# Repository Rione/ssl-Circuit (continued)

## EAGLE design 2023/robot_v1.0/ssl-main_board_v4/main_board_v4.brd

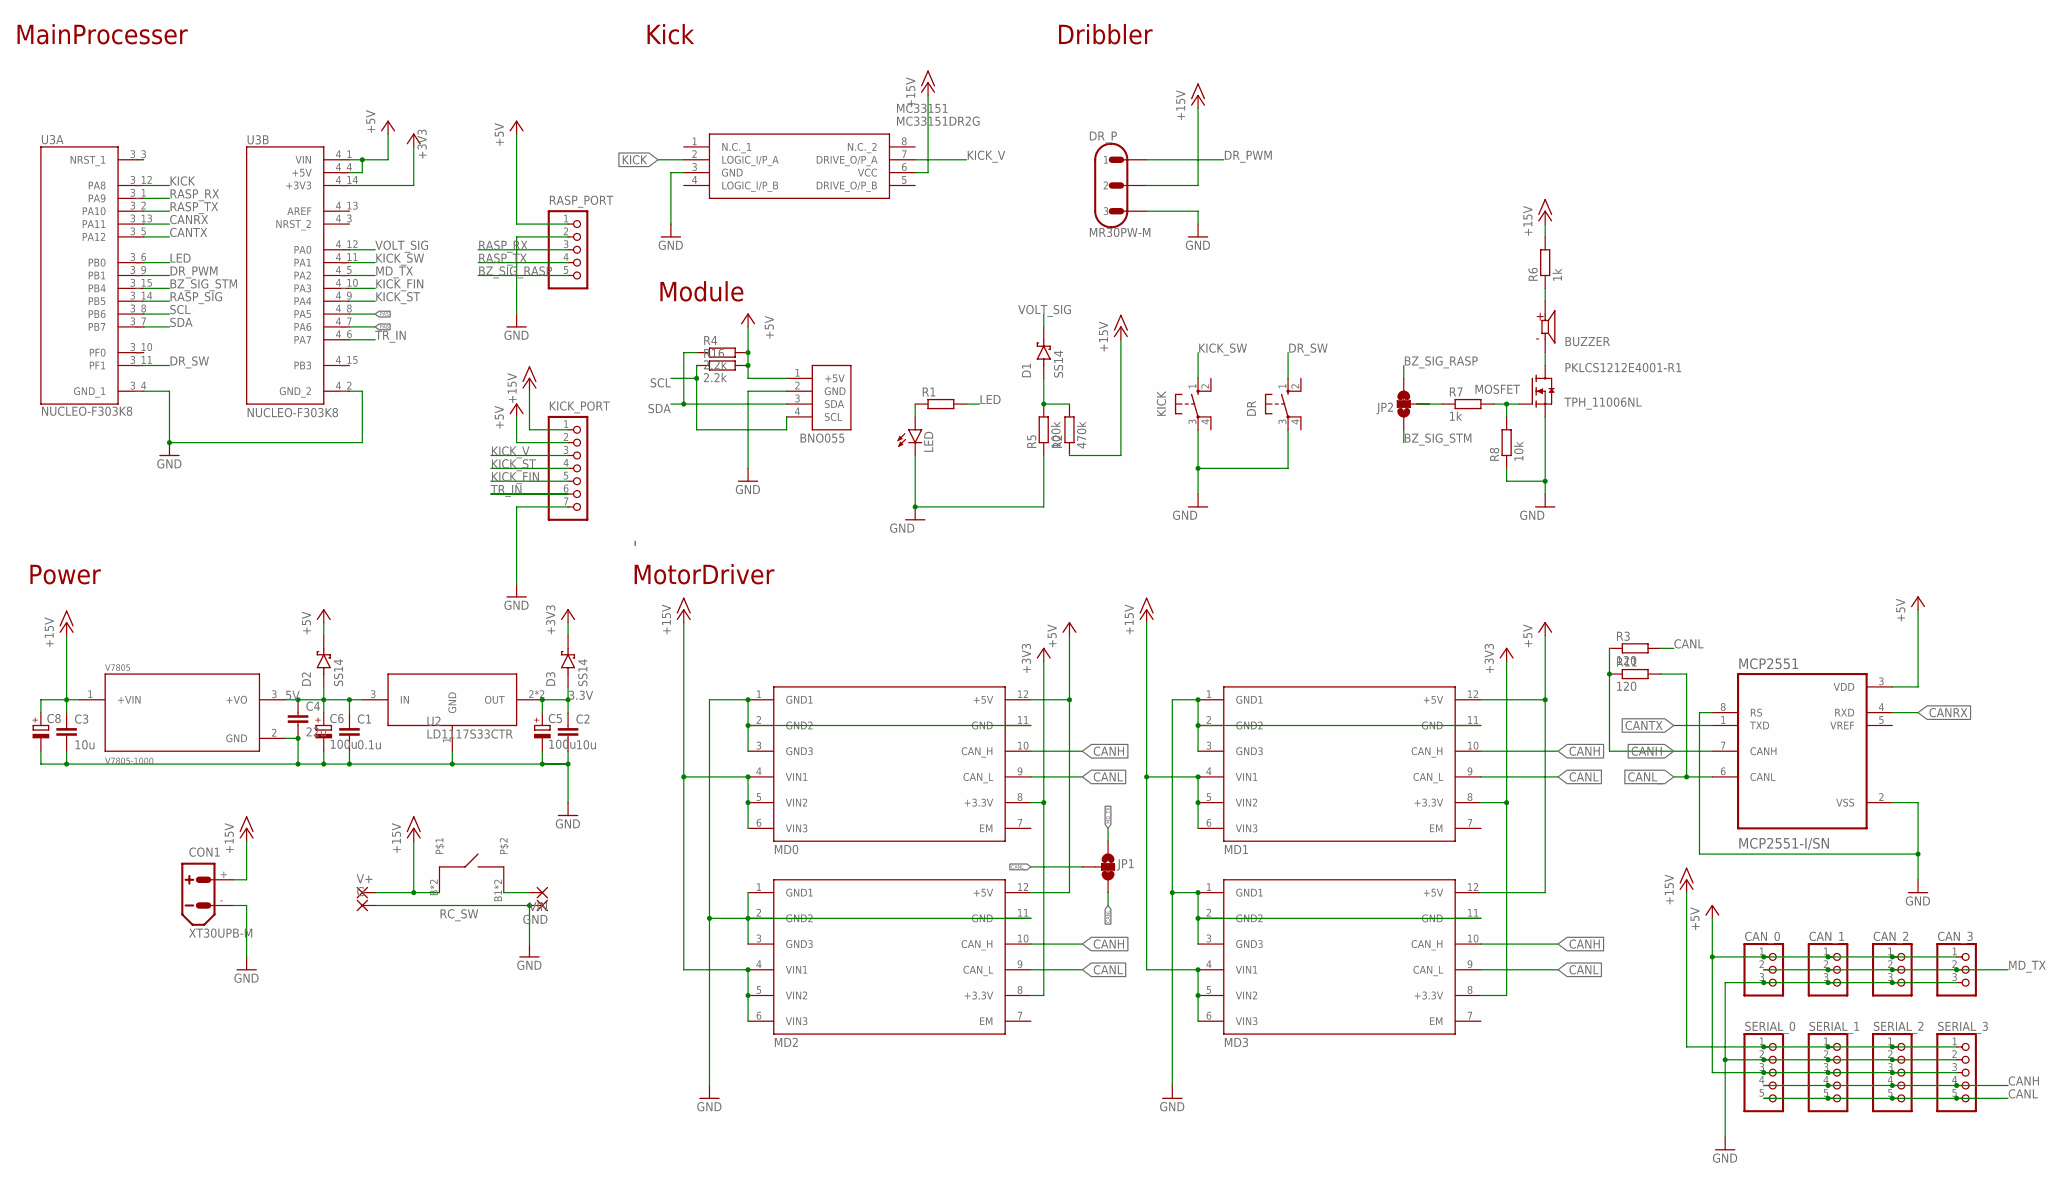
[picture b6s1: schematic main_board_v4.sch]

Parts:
BUZZER: PKLCS1212E4001-R1; SPKR_PKLCS1212E4001-R1
C1: 0.1u; C1608
C2, C3: 10u; C1608
C4: 22u; C2012
C5, C6: 100u; 153CLV-0605
C8: CPOL-EU140CLH-1010; 140CLH-1010
CAN_0, CAN_1, CAN_2, CAN_3: PINHD-1X3; 1X03
CON1: XT30UPB-M
D1, D2, D3: SS14; DIOM4325X250N
DR: 10-XX; B3F-10XX
DR_P: MR30PW-M
G: SMD2; SMD1,27-2,54
GND: SMD5; SMD2,54-5,08
JP1, JP2: JUMPER-SMT_3_1-NC_TRACE_SILK; SMT-JUMPER_3_1-NC_TRACE_SILK
KICK: 10-XX; B3F-10XX
KICK_PORT: S7B-XH-A
LED: LEDCHIP-LED0805; CHIP-LED0805
MC33151: MC33151DR2G; SOIC127P600X175-8N
MCP2551: MCP2551-I/SN; SOIC127P599X175-8N
MD0, MD1, MD2, MD3: MD_ROOTS
MOSFET: TPH_11006NL; TRANS_TPHR8504PL,L1Q
R1: R-EU_R0603; R0603
R2: 470k; R0603
R3, R11: 120; R0603
R4, R16: 2.2k; R0603
R5: 100k; R0603
R6, R7: 1k; R0603
R8: 10k; R0603
RASP_PORT: B5B-XH-A
SERIAL_0, SERIAL_1, SERIAL_2, SERIAL_3: PINHD-1X5; 1X05
U2: LD1117S33CTR; SOT223
U3: NUCLEO-F303K8; MODULE_NUCLEO-F303K8
U$1: BNO055
U$2: ROCKER_SW; MILLING
V7805: V7805-1000; CONV_V7805-1000
V+: SMD2; SMD1,27-2,54
VIN: SMD5; SMD2,54-5,08

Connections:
2: D1.A, R2.2, R5.2
3.3V: C2.1, C5.+, D3.A, U2.2 (OUT), U2.4 (OUT)
5V: C1.1, C4.1, C6.+, D2.A, U2.3 (IN), V7805.3 (+VO)
+3V3: D3.C (K), MD0.8 (+3.3V), MD1.8 (+3.3V), MD2.8 (+3.3V), MD3.8 (+3.3V), U3.4_14 (+3V3)
+5V: CAN_0.1, CAN_1.1, CAN_2.1, CAN_3.1, D2.C (K), KICK_PORT.2, MCP2551.3 (VDD), MD0.12 (+5V), MD1.12 (+5V), MD2.12 (+5V), MD3.12 (+5V), R4.2, R16.2, RASP_PORT.1, SERIAL_0.3, SERIAL_1.3, SERIAL_2.3, SERIAL_3.3, U3.4_1 (VIN), U3.4_4 (+5V), U$1.1 (+5V)
+15V: C3.1, C8.+, CON1.+, DR_P.2, KICK_PORT.1, MC33151.6 (VCC), MD0.4 (VIN1), MD0.5 (VIN2), MD0.6 (VIN3), MD1.4 (VIN1), MD1.5 (VIN2), MD1.6 (VIN3), MD2.4 (VIN1), MD2.5 (VIN2), MD2.6 (VIN3), MD3.4 (VIN1), MD3.5 (VIN2), MD3.6 (VIN3), R2.1, R6.2, SERIAL_0.1, SERIAL_1.1, SERIAL_2.1, SERIAL_3.1, U$2.B, U$2.T, V7805.1 (+VIN), V+.1
BZ_SIG: JP2.2, R7.1
BZ_SIG_RASP: JP2.3, RASP_PORT.5
BZ_SIG_STM: JP2.1, U3.3_15 (PB4)
CANH: MCP2551.7 (CANH), MD0.10 (CAN_H), MD1.10 (CAN_H), MD2.10 (CAN_H), MD3.10 (CAN_H), R3.1, R11.1, SERIAL_0.4, SERIAL_1.4, SERIAL_2.4, SERIAL_3.4
CANL: JP1.3, MD0.9 (CAN_L), MD1.9 (CAN_L), MD2.9 (CAN_L), MD3.9 (CAN_L), R3.2, SERIAL_0.5, SERIAL_1.5, SERIAL_2.5, SERIAL_3.5
CANL_: JP1.2, MCP2551.6 (CANL), R11.2
CANRX: MCP2551.4 (RXD), U3.3_13 (PA11)
CANTX: MCP2551.1 (TXD), U3.3_5 (PA12)
DR_PWM: DR_P.1, U3.3_9 (PB1)
DR_SW: DR.1 (S), U3.3_11 (PF1)
GND: C1.2, C2.2, C3.2, C4.2, C5.-, C6.-, C8.-, CAN_0.3, CAN_1.3, CAN_2.3, CAN_3.3, CON1.-, DR.3, DR_P.3, G.1, GND.1, KICK.3, KICK_PORT.7, LED.C, MC33151.3 (GND), MCP2551.2 (VSS), MCP2551.8 (RS), MD0.1 (GND1), MD0.2 (GND2), MD0.3 (GND3), MD0.11 (GND), MD1.1 (GND1), MD1.2 (GND2), MD1.3 (GND3), MD1.11 (GND), MD2.1 (GND1), MD2.2 (GND2), MD2.3 (GND3), MD2.11 (GND), MD3.1 (GND1), MD3.2 (GND2), MD3.3 (GND3), MD3.11 (GND), MOSFET.1 (S), MOSFET.2 (S), MOSFET.3 (S), R5.1, R8.1, RASP_PORT.2, SERIAL_0.2, SERIAL_1.2, SERIAL_2.2, SERIAL_3.2, U2.1 (GND), U3.3_4 (GND_1), U3.4_2 (GND_2), U$1.2 (GND), V7805.2 (GND)
KICK: MC33151.2 (LOGIC_I/P_A), U3.3_12 (PA8)
KICK_FIN: KICK_PORT.5, U3.4_10 (PA3)
KICK_ST: KICK_PORT.4, U3.4_9 (PA4)
KICK_SW: KICK.1 (S), U3.4_11 (PA1)
KICK_V: KICK_PORT.3, MC33151.7 (DRIVE_O/P_A)
LED: R1.2, U3.3_6 (PB0)
MD_TX: CAN_0.2, CAN_1.2, CAN_2.2, CAN_3.2, JP1.1, U3.4_5 (PA2)
unnamed: MOSFET.4 (G), R7.2, R8.2
unnamed: BUZZER.N, MOSFET.5 (D), MOSFET.6 (D), MOSFET.7 (D), MOSFET.8 (D), MOSFET.9 (D)
unnamed: LED.A, R1.1
unnamed: BUZZER.P, R6.1
PA5: U3.4_8 (PA5)
PA6: U3.4_7 (PA6)
RASP_RX: RASP_PORT.3, U3.3_1 (PA9)
RASP_SIG: U3.3_14 (PB5)
RASP_TX: RASP_PORT.4, U3.3_2 (PA10)
SCL: R16.1, U3.3_8 (PB6), U$1.4 (SCL)
SDA: R4.1, U3.3_7 (PB7), U$1.3 (SDA)
TR_IN: KICK_PORT.6, U3.4_6 (PA7)
VIN: U$2.B1, U$2.T1, VIN.1
VOLT_SIG: D1.C (K), U3.4_12 (PA0)

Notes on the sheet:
Module
Power
Kick
Dribbler
MotorDriver
MainProcesser

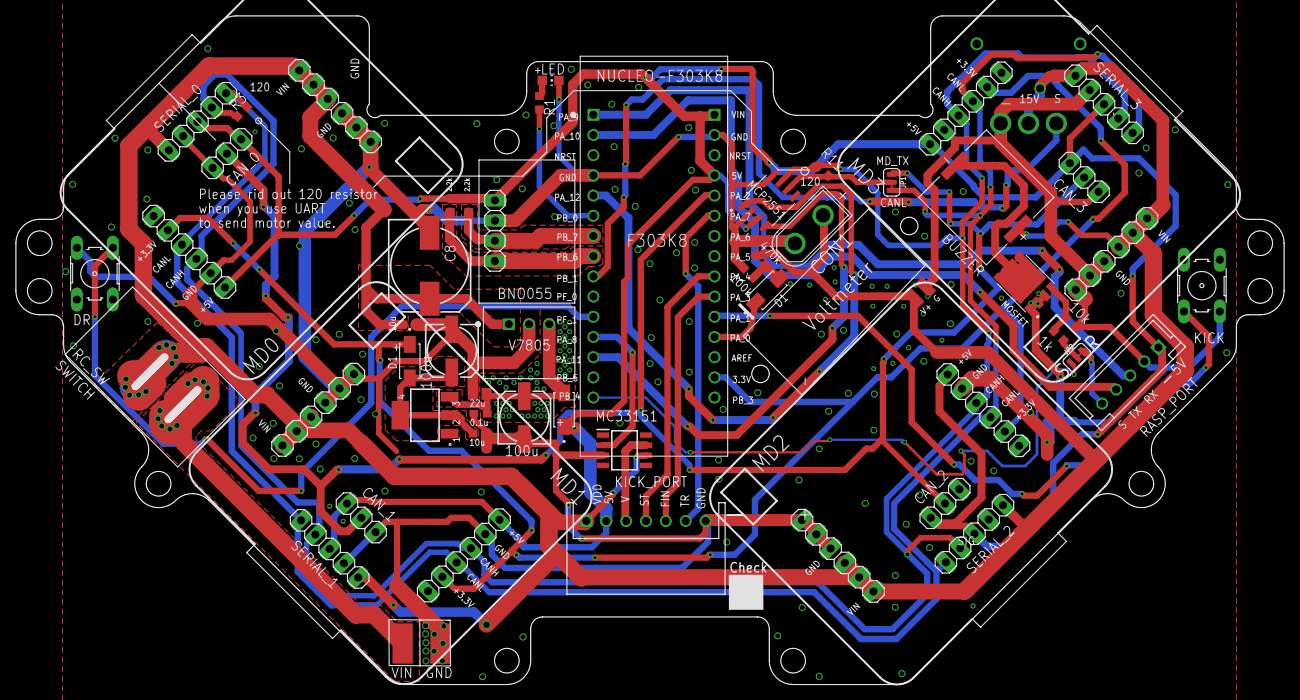
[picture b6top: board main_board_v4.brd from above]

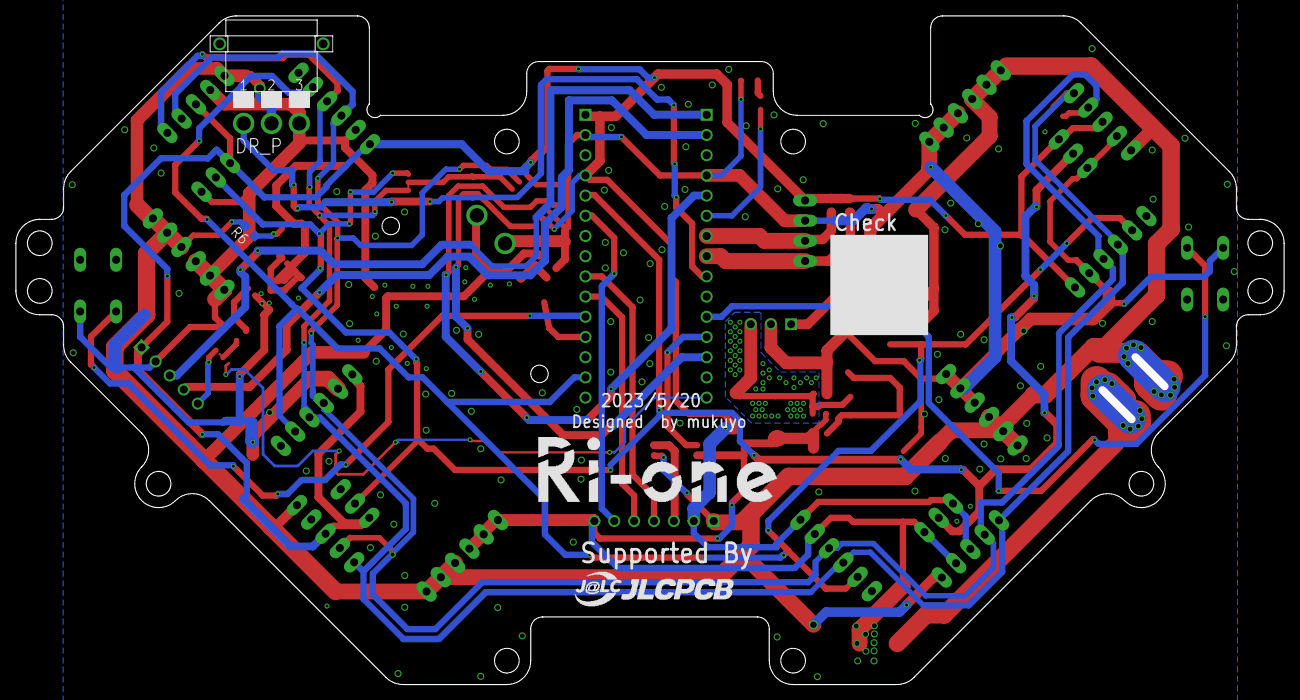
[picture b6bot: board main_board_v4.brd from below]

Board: 2 copper layers, 159.5 x 84.1 mm, 54 parts (2 on the bottom side), 35 nets.

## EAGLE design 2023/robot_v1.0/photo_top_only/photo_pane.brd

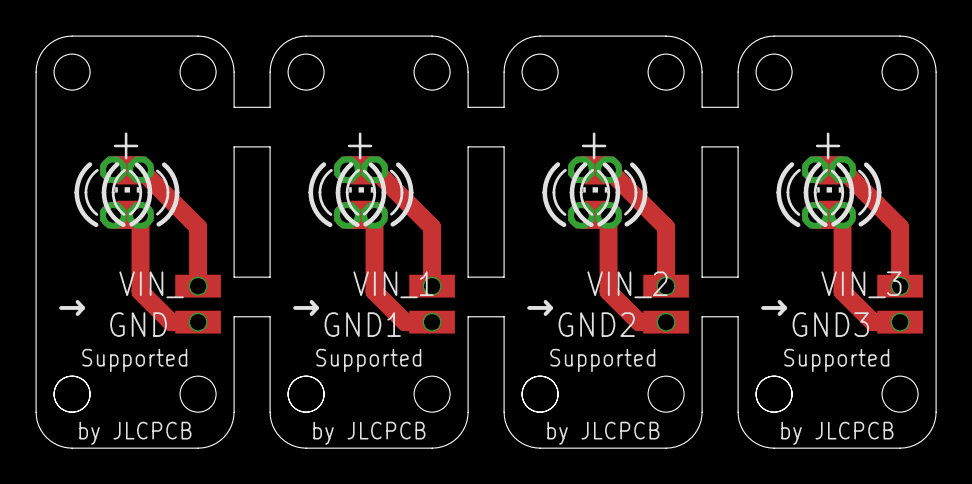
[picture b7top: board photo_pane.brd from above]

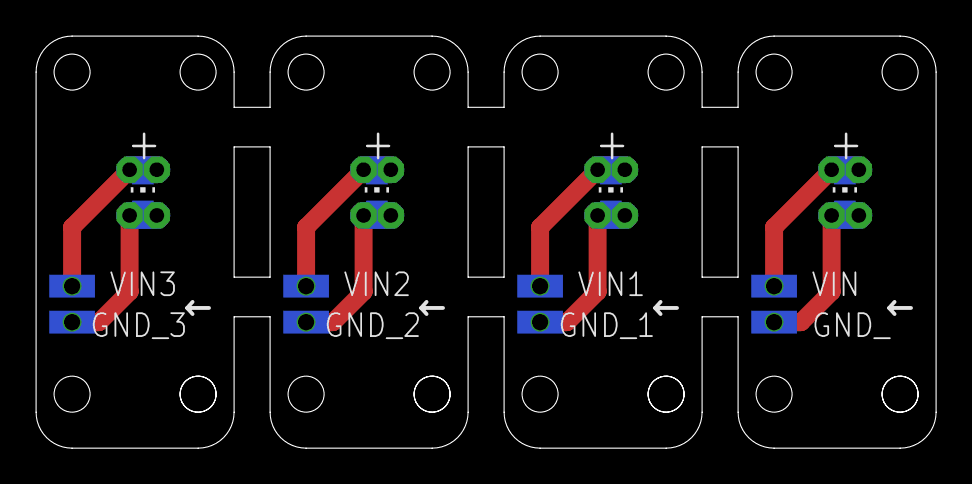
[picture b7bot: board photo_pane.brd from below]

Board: 2 copper layers, 50.0 x 22.9 mm, 32 parts (12 on the bottom side), 8 nets.

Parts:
GND, GND1, GND2, GND3: SMD1,27-2,54
GND_, GND_1, GND_2, GND_3: SMD1,27-2,54
LED1, LED3, LED5, LED6, LED9, LED10, LED13, LED14: CHIP-LED0805
LED2, LED4, LED7, LED8, LED11, LED12, LED15, LED16: TLLR4400; LED3MM
VIN, VIN1, VIN2, VIN3: SMD1,27-2,54
VIN_, VIN_1, VIN_2, VIN_3: SMD1,27-2,54

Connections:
unnamed: GND1.1, GND_1.1, LED1.A, LED6.A, LED7.A, LED8.A
unnamed: LED1.C, LED6.C, LED7.K, LED8.K, VIN1.1, VIN_1.1
unnamed: LED2.K, LED3.C, LED4.K, LED5.C, VIN.1, VIN_.1
unnamed: GND2.1, GND_2.1, LED9.A, LED10.A, LED11.A, LED12.A
unnamed: GND.1, GND_.1, LED2.A, LED3.A, LED4.A, LED5.A
unnamed: LED9.C, LED10.C, LED11.K, LED12.K, VIN2.1, VIN_2.1
unnamed: GND3.1, GND_3.1, LED13.A, LED14.A, LED15.A, LED16.A
unnamed: LED13.C, LED14.C, LED15.K, LED16.K, VIN3.1, VIN_3.1

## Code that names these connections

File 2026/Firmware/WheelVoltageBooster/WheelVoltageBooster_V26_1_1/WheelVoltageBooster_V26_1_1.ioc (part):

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Mcu.Name=STM32H523CEUx
Mcu.Package=UFQFPN48
Mcu.UserName=STM32H523CEUx
PA0.GPIOParameters=GPIO_PuPd,GPIO_Label,GPIO_Mode
PA0.GPIO_Label=MVC_VSCAN1
PA0.GPIO_Mode=GPIO_MODE_ANALOG
PA0.GPIO_PuPd=GPIO_NOPULL
PA0.Signal=ADCx_INP0
PA1.GPIOParameters=GPIO_PuPd,GPIO_Label,GPIO_Mode
PA1.GPIO_Label=MVC_VSCAN2
PA1.GPIO_Mode=GPIO_MODE_ANALOG
PA1.GPIO_PuPd=GPIO_NOPULL
PA1.Signal=ADCx_INP1
PA11.Mode=FDCAN_Activate
PA11.Signal=FDCAN1_RX
PA12.Mode=FDCAN_Activate
PA12.Signal=FDCAN1_TX
PA2.GPIOParameters=GPIO_PuPd,GPIO_Label,GPIO_Mode
PA2.GPIO_Label=MVC_IOUT2
PA2.GPIO_Mode=GPIO_MODE_ANALOG
PA2.GPIO_PuPd=GPIO_NOPULL
PA2.Signal=ADCx_INP14
PA3.GPIOParameters=GPIO_PuPd,GPIO_Label,GPIO_Mode
PA3.GPIO_Label=MVC_IOUT1
PA3.GPIO_Mode=GPIO_MODE_ANALOG
PA3.GPIO_PuPd=GPIO_NOPULL
PA3.Signal=ADCx_INP15
PA4.GPIOParameters=GPIO_PuPd,GPIO_Label,GPIO_Mode
PA4.GPIO_Label=MVC_TMP
PA4.GPIO_Mode=GPIO_MODE_ANALOG
PA4.GPIO_PuPd=GPIO_NOPULL
PA4.Signal=ADCx_INP18
PA5.GPIOParameters=GPIO_Label
PA5.GPIO_Label=MVC_DIR
PA5.Signal=GPIO_Output
PA6.GPIOParameters=GPIO_Label
PA6.GPIO_Label=MVC_EN2
PA6.Signal=GPIO_Output
PA7.GPIOParameters=GPIO_Label
PA7.GPIO_Label=MVC_ISETD
PA7.Signal=S_TIM3_CH2
PA8.GPIOParameters=GPIO_Label
PA8.GPIO_Label=FAN_EN
PA8.Signal=GPIO_Output
PB0.GPIOParameters=GPIO_Label
PB0.GPIO_Label=MVC_UVLO
PB0.Signal=S_TIM3_CH3
PB1.GPIOParameters=GPIO_Label
PB1.GPIO_Label=MVC_EN1
PB1.Signal=GPIO_Output
PB10.GPIOParameters=GPIO_Label
PB10.GPIO_Label=SVC_EN
PB10.Signal=GPIO_Output
PB14.GPIOParameters=GPIO_Speed
PB14.GPIO_Speed=GPIO_SPEED_FREQ_VERY_HIGH
PB14.Mode=Asynchronous
PB14.Signal=USART1_TX
PB15.GPIOParameters=GPIO_Speed
PB15.GPIO_Speed=GPIO_SPEED_FREQ_VERY_HIGH
PB15.Mode=Asynchronous
PB15.Signal=USART1_RX
PB4(NJTRST).GPIOParameters=GPIO_Label
PB4(NJTRST).GPIO_Label=LED_CAN
PB4(NJTRST).Signal=GPIO_Output
PB5.GPIOParameters=GPIO_Label
PB5.GPIO_Label=LED_3
PB5.Signal=GPIO_Output
PB6.GPIOParameters=GPIO_Label
PB6.GPIO_Label=LED_2
PB6.Signal=GPIO_Output
PB7.GPIOParameters=GPIO_Label
PB7.GPIO_Label=LED_1
PB7.Signal=GPIO_Output
PB8.GPIOParameters=GPIO_Label
PB8.GPIO_Label=USW
PB8.Signal=GPIO_Input
PH0-OSC_IN(PH0).Mode=HSE-External-Oscillator
PH0-OSC_IN(PH0).Signal=RCC_OSC_IN
PH1-OSC_OUT(PH1).Mode=HSE-External-Oscillator
PH1-OSC_OUT(PH1).Signal=RCC_OSC_OUT
RCC.HSE_VALUE=16000000
RCC.SYSCLKFreq_VALUE=240000000
RCC.SYSCLKSource=RCC_SYSCLKSOURCE_PLLCLK
board=custom

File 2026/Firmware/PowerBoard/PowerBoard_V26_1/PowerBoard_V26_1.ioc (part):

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Mcu.Name=STM32F303K(6-8)Tx
Mcu.Package=LQFP32
Mcu.UserName=STM32F303K8Tx
PA1.Signal=S_TIM2_CH2
PA10.Mode=Asynchronous
PA10.Signal=USART1_RX
PA11.Mode=CAN_Activate
PA11.Signal=CAN_RX
PA12.Mode=CAN_Activate
PA12.Signal=CAN_TX
PA13.Mode=Serial_Wire
PA13.Signal=SYS_JTMS-SWDIO
PA14.Mode=Serial_Wire
PA14.Signal=SYS_JTCK-SWCLK
PA15.GPIOParameters=GPIO_Label
PA15.GPIO_Label=LT_DISCHARGE
PA15.Signal=GPIO_Output
PA2.Signal=S_TIM2_CH3
PA3.GPIOParameters=GPIO_Label
PA3.GPIO_Label=LED
PA3.Signal=S_TIM2_CH4
PA8.GPIOParameters=GPIO_PuPd,GPIO_Label
PA8.GPIO_Label=BUTTON
PA8.GPIO_PuPd=GPIO_PULLUP
PA8.Signal=GPIO_Input
PA9.Mode=Asynchronous
PA9.Signal=USART1_TX
PB0.Mode=IN11-Single-Ended
PB0.Signal=ADC1_IN11
PB1.Mode=IN12-Single-Ended
PB1.Signal=ADC1_IN12
PB6.GPIOParameters=GPIO_Label
PB6.GPIO_Label=LT_CHARGE
PB6.Signal=GPIO_Output
PB7.GPIOParameters=GPIO_Label
PB7.GPIO_Label=LT_DONE
PB7.Signal=GPIO_Input
PF0\ /\ OSC_IN.Mode=HSE-External-Oscillator
PF0\ /\ OSC_IN.Signal=RCC_OSC_IN
PF1\ /\ OSC_OUT.Mode=HSE-External-Oscillator
PF1\ /\ OSC_OUT.Signal=RCC_OSC_OUT
RCC.HSEPLLFreq_Value=4000000
RCC.HSE_VALUE=16000000
RCC.SYSCLKFreq_VALUE=60000000
RCC.SYSCLKSourceVirtual=RCC_SYSCLKSOURCE_PLLCLK
board=custom

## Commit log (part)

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2025-12-08 配置一旦終わり。一部仮置き
2025-12-09 MX設定変更
2025-12-09 書き込み成功
2025-12-09 BLDC強制転流成功
2025-12-10 配線途中経過
2025-12-10 time_ms設定
2025-12-10 STSPIN32G4回り修正
2025-12-10 階層シート追加
2025-12-10 アナログスイッチ追加
2025-12-10 書き込み系統のバス追加
2025-12-10 メイン基板ひとまず完成
2025-12-10 一部修正
2025-12-10 スイッチングの配線終わり
2025-12-11 回路図修正終わり
2025-12-13 部品配置終わり
2025-12-13 位置調整
2025-12-13 配線途中 =^.^= !!!!!????
2025-12-15 軽微な修正・追加、JLCPCB発注
2025-12-17 設計終わり
2025-12-17 製造ファイル出力
2025-12-17 配線の修正終わり
2025-12-17 シルク修正
2025-12-17 フットプリント変更
2025-12-17 位置修正
2025-12-17 製造ファイル再出力
2025-12-17 最終確認完了
2025-12-23 cで使えるライブラリを個人のプロジェクトからコピペ
2025-12-23 canのライブラリ追加
2025-12-23 中央値フィルタと移動平均フィルタの追加
2025-12-23 pidのライブラリ追加
2025-12-23 cubeMX生成
2025-12-23 ピン割り当て変更
2025-12-24 PWM周波数決定
2025-12-24 make通った
2025-12-24 基本的な枠組みは作った
2026-01-23 canの送受信プログラム
2026-01-27 回路修正終わり
2026-01-30 canライブラリのファイル名変更
2026-01-30 シリアルのバグ修正
2026-01-30 シリアルの修正
2026-01-30 MXで生成
2026-01-30 ピン再定義
2026-01-30 makefile編集
2026-01-30 大体の枠組みは作った
2026-01-30 最低限動作するのに必要な機能
2026-01-30 パラメータを同一ファイルで管理
2026-01-30 オムニホイールの制御まわり
2026-02-06 シリアル周りの構築途中
2026-02-11 モーター制御用のプログラム完成
2026-02-11 キッカー周りのプログラムできた
2026-02-11 uiの追加とgoogle c++ style guideに準拠した規則に変更
2026-02-11 Rockとの通信追加とバグ修正
2026-02-12 キッカーの処理更新
2026-02-12 main_modeの処理実装
2026-02-14 ローカルコントロール用の場所作った
2026-02-14 uiからロボットを操作できるように
2026-02-14 ロボットを完全に静止させれる関数
2026-02-17 V2開始、配置完了、配線やり直し
2026-02-21 プログラムをユニット分割した
2026-02-23 修正、製造ファイル出力
2026-02-23 修正、出力
2026-02-27 SPIのライブラリ追加
2026-02-27 cubeMXで生成した
2026-03-01 makefile周辺環境の整備
2026-03-01 cubeMX側での修正
2026-03-01 can以外の初期化処理プログラム
2026-03-17 回路微修正
2026-03-18 電源周り途中
2026-03-29 test
2026-04-09 電源、UI、LED 仮完成
2026-04-10 daplink対応
2026-04-10 serial.h を HAL マクロ版に書き換え
2026-04-10 バグ修正
2026-04-12 can受信
2026-04-13 can送受信確認
2026-04-13 全機能実装完了
2026-04-13 motor_drive.cppを統合
2026-04-13 motor_drive.cpp修正
2026-04-16 りくさんデバッグ
2026-04-16 dapで書き込めるように
2026-04-21 書き込み方法変更
2026-04-23 書き込み修正
2026-04-25 3.3V配線以外完了
2026-04-25 ADCピン修正、V2仮完成
2026-04-27 モーターのフリー状態追加
2026-04-27 Initial plan
2026-04-27 リファクタリング：ドリブラーロジックをモジュール化し、改良されたモーター制御による構造化されたボールキャプチャ検出を実装
2026-04-27 全機能動いた
2026-04-27 検出精度向上
2026-04-27 リフォーマット
2026-04-27 CubeMXからジェネレート
2026-04-27 MXピン設定半分くらい完了
2026-04-27 基本構成完成
2026-04-28 test削除
2026-04-28 ピン設定変更
2026-04-28 モニター位置修正中
2026-04-28 ADC読めた
2026-04-29 モニター位置修正完了
2026-04-30 配線完了
2026-04-30 シルク途中（仮）
2026-05-01 電源周り修正
2026-05-07 スイッチのプルアップ追加
2026-05-07 Revert "スイッチのプルアップ追加"
    This reverts commit 9a7fb44406ff4e7d744a04be1ec33d86a56250bd.
2026-05-07 V2完成、JLCPCB発注
2026-05-11 Update ADC sampling time and adjust BLDC control parameters for improved performance
2026-05-14 速度制御のプログラム修正
2026-05-14 flash libraryをF303，F446，G431全てのマイコンに対応
2026-05-14 ファイル生成
2026-05-19 V1からコピー
2026-05-19 修正&製造ファイル出力
2026-05-22 全てCに置き換え
2026-05-22 UART関連の設定
2026-05-22 MX 編集
2026-05-22 Lチカ・ハートビート確認
2026-05-27 README.md を作成
2026-05-27 README.md を更新
2026-05-27 README.md の削除 場所を間違えたため
2026-05-27 kalman filter for robot speed using BMI270
2026-06-11 WIP エンコーダー値送信
2026-06-12 受信のみ未確認だが他は全部完成
2026-06-12 パケット変更
2026-06-12 モーター受信パケット変更
2026-06-12 キック力調整
2026-06-12 （失敗）MDとメイン基板の通信テスト
2026-06-12 受信パケット変更
2026-06-12 MD送信
2026-06-12 printf削除
2026-06-12 UART周波数変更
2026-06-12 電圧読めた？値はあるけど不明
2026-06-13 new_display_image
2026-06-13 add_change
2026-06-18 Rock5AとSPI通信できた
2026-06-18 電源を入れ直しても回るようにした
2026-06-19 ゲイン調整
2026-06-19 IGBTが壊れないようにソフトを詰めた(失敗)
2026-06-20 Fix sidebar duplication and velocity text overlapping
2026-06-22 2026: UI test mode and charge display bug fixed (baseline before checksum)
2026-06-22 理想ダイオード追加
2026-06-23 パラメータ調整
2026-06-23 MakefileにOS分岐追加
2026-06-24 feat: 2026 UI modernization and safety interlocks update
2026-06-25 2024ファームウェアを2025に統一(ホイール角速度受信など)
2026-06-25 fix: limit UI transmission frequency to 10Hz
2026-06-25 feat: Implement motor-to-wheel scaling and update CAN message handling for motor angular velocities
2026-06-25 Implement USART2 interrupt handling and error recovery for improved stability
2026-06-25 feat: Add USART configuration and interrupt handling for USART2
2026-06-25 Refactor serial reception logic and adjust timing for gate driver configuration
2026-06-25 Enhance gate driver recovery logic and add WAKE function for fault handling
2026-06-25 (旧機体)静止時にもモーターから角速度を取得できるように・500fps→60fpsで送るように変更
2026-06-25 (旧機体)canのコンセン問題カイエkつだ
2026-06-25 ちゃんと動いた(原因はプルアップの設定)
2026-06-25 放電方法変更&can送信パケット変更
2026-06-25 feat: Add DAPFlash script for flashing firmware and update Makefile; refactor kicker and robot modules for improved functionality
2026-06-25 fix: Restore OmniDrive_SetFree in LocalController_Stop and remove debug print in Robot_UpdateSensor
2026-06-25 fix: Update OmniDrive velocity handling and improve Robot sensor transmission
2026-06-25 fix: Adjust wheel linear velocity calculation in OmniDrive_SetVel for accurate motor control
2026-06-26 fix: Update Robot_RockBuildTxPacket function signature and adjust wheel data transmission in SPI packet
2026-06-26 (旧機体)2025のメインFWでconfigファイルを編集したらドリブラーを新旧選択できるようにした
2026-06-26 (旧機体)受信バッファのタイムアウトリセット実装
2026-06-26 feat: add 8 seconds display sleep timeout and TFT sleep commands
2026-06-26 feat: Enhance BufferedSerial with error handling and DMA management
    - Added functions to register and find serial instances.
    - Implemented error handling for UART reception errors.
    - Introduced methods to start and restart DMA for receiving data.
    - Updated the BufferedSerial class to manage reception errors and maintain state.
2026-06-26 Update UI serial transmission to 21 bytes to match new XIAO UI
2026-06-26 Fix UI recv missing from main loop
2026-06-26 Fix 2025 UI and STM32 compatibility and bugs
    - Replaced 2025 ui_RP2040 with 2026 ui_MainBoard structure
    - Fixed uiStatus bitfield in STM32 to match 2026 modeStatus structure (charge_state is now properly received)
    - Disabled 15-second timeout in STM32 that caused automatic discharge
    - Set DRIBBLER_VERSION to NEW in config.h to support new dribbler board
    - Updated Motor Test speed to 500mm/s to overcome static friction
2026-06-26 Fix UI tests bypassing and kicker charging logic for 2025 firmware
    - Fix capValEstimate underflow causing Kicker failures
    - Disable auto-charge fallback to Pi to allow manual control
    - Bypass E-Stop for UI Motor/Dribbler tests to prevent Pi serial noise interference
2026-06-26 Allow execution of Dribbler and Motor Test without charging
    - UI (RP2040): Removed charge state check for Dribbler and Motor Test buttons.
    - STM32 (F446RE): Removed logic that forces test flags to cancel upon receiving Discharge command.
2026-06-27 fix: Remove commented OmniDrive_SetVel call in LocalController_Stop and streamline Robot_SendOmniDrive function for direct velocity setting
2026-06-27 Adjust serial send interval and refine PID controller gains for improved performance
2026-06-27 Adjust low speed gain maximum value for improved control stability
2026-06-27 fix: Enhance wheel angular velocity calculation in OmniDrive_SetVel with constraints for maximum speed
2026-06-27 fix: Update Robot_RockBuildTxPacket comment to reflect correct data packet size
2026-06-27 Add low-pass filter for angular speed and update serial send logic
2026-06-27 Adjust control parameters and improve photo threshold for enhanced performance
2026-06-27 Define CAN_SEND_ID for improved readability and maintainability
2026-06-27 OS分岐追加(Win - Mac)
2026-06-27 Adjust kick PWM duty cycle limit and remove redundant kick output reset
2026-06-27 mainからドリブラー動かせた
2026-06-28 do_directを実装した
2026-06-28 キッカードリブラー周りのリファクタリング
2026-06-28 CANの割り込み開始時間を変更
2026-06-28 do_directの調整
2026-06-28 フォトの値が変わった瞬間にcanをトリガー
2026-06-28 SPIにヘッダフッタを追加
2026-06-28 Update UI colors, testMode layout, and dribbler configuration
2026-06-28 Add charge control logic to KickerBoard in Camera and Main modes
    - Implemented charge control in CameraMode and MainMode to manage kicker charging based on robot status.
    - Updated KickerBoard header comments for clarity on charge and discharge states.
2026-06-28 Update project paths and enhance KickerBoard functionality
    - Updated file paths in VSCode configuration for new user environment.
    - Enhanced KickerBoard with charge feedback logic to improve charge state management.
    - Modified robot control logic in CameraMode and MainMode to respect user input timing for charge control.
    - Improved UI handling for charge and discharge commands in testMode.
2026-06-28 SPIエラー率を減らした
2026-06-28 ADCオーバサンプリングを入れてノイズを減らした
2026-06-29 コンデンサの値読めるように&チップキックできない問題
2026-06-30 Revert "ADCオーバサンプリングを入れてノイズを減らした"
    This reverts commit 83566f72cafb6befc28337296ca4fcb2ab6d357c.
2026-06-30 ADC精度改善
2026-06-30 ホイールロックの検知
2026-06-30 n_faultのプルアップ
2026-06-30 速度計算単純化
2026-06-30 チャージ・放電のcanの周期制限
2026-06-30 LED表示
2026-06-30 LED表示変更
2026-06-30 キッカー威力調整
